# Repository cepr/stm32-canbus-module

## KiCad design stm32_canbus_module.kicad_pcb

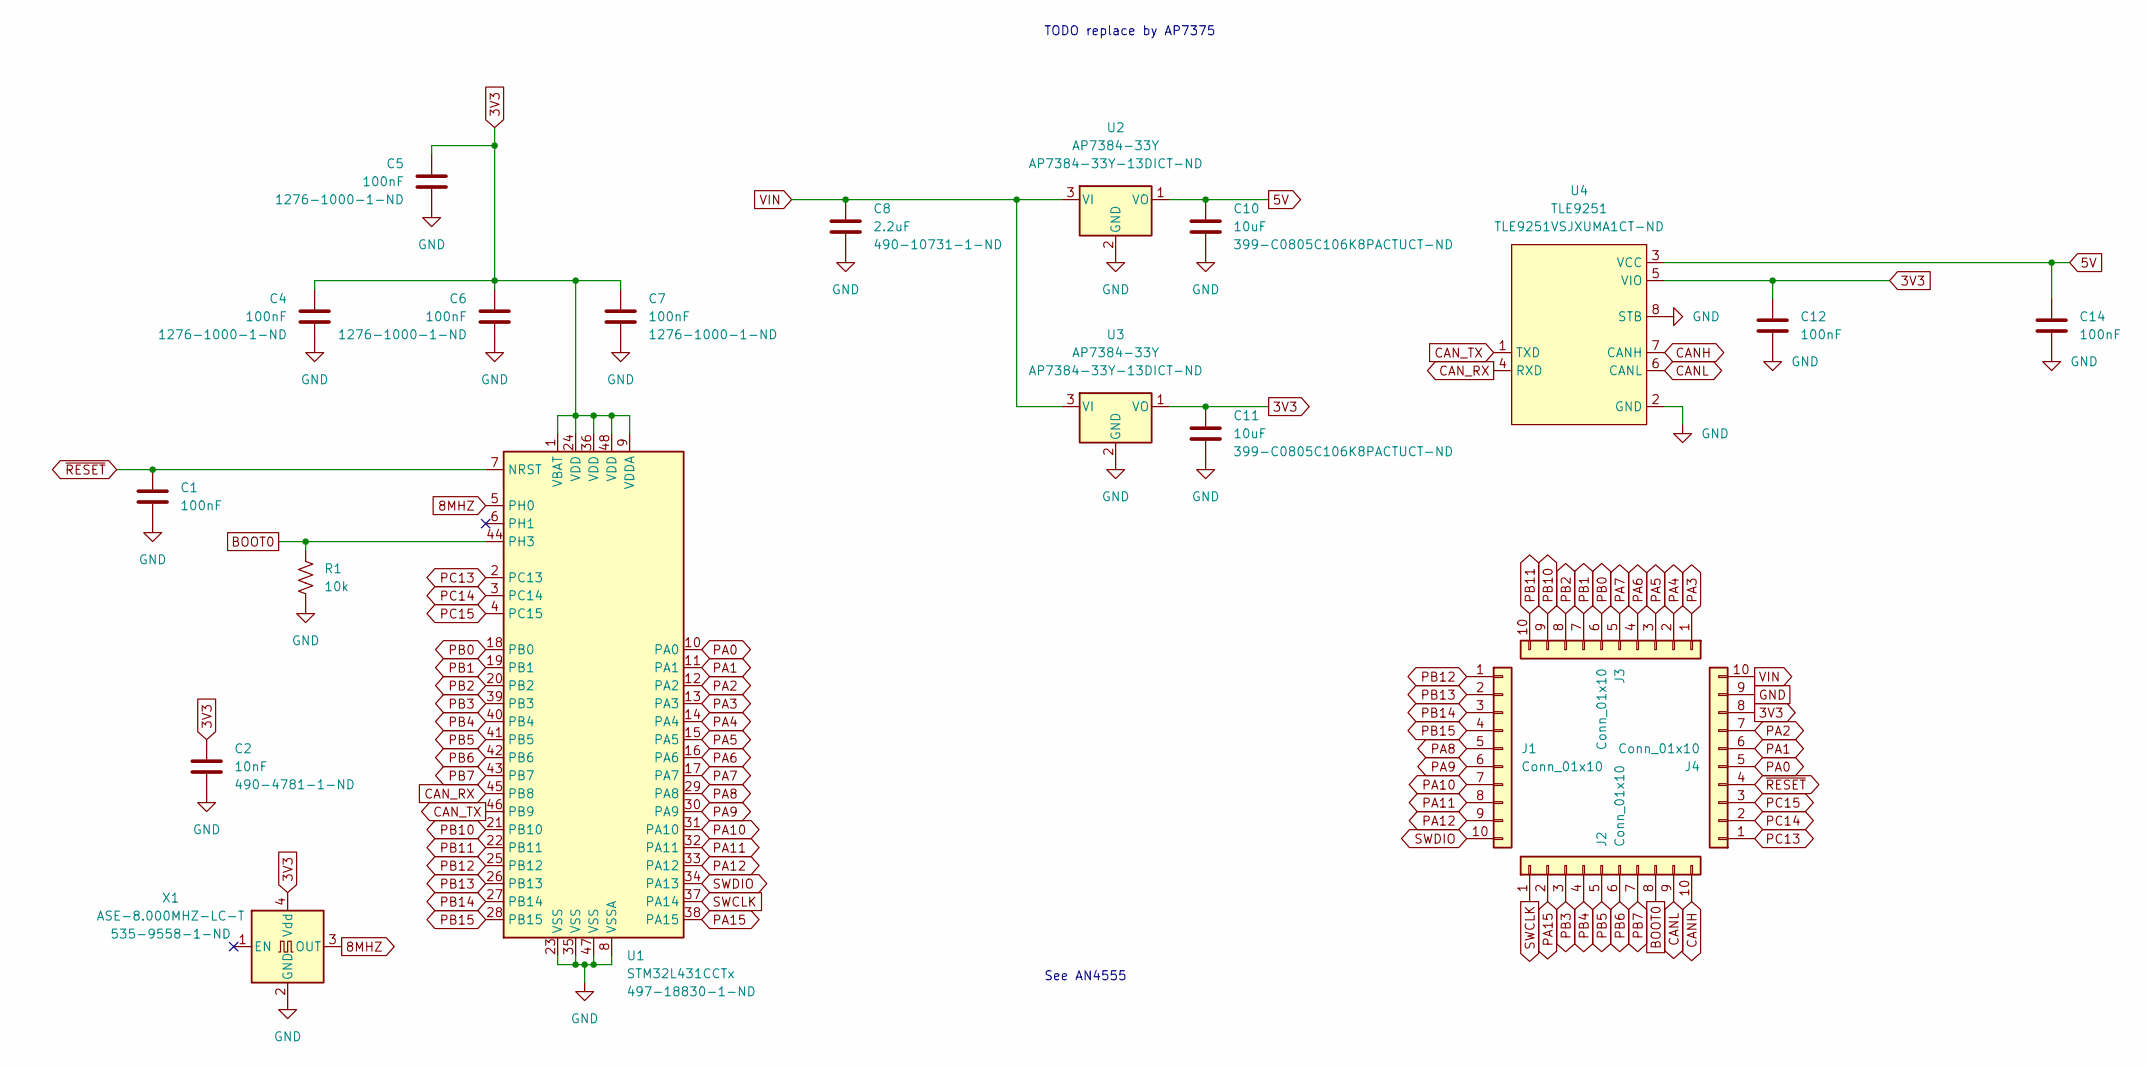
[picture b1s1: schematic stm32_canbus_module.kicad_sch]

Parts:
C1, C4, C5, C6, C7, C12, C14: 100nF; C_0603_1608Metric_Pad1.08x0.95mm_HandSolder; DigiKey 1276-1000-1-ND
C2: 10nF; C_0603_1608Metric_Pad1.08x0.95mm_HandSolder; DigiKey 490-4781-1-ND
C8: 2.2uF; C_0603_1608Metric_Pad1.08x0.95mm_HandSolder; DigiKey 490-10731-1-ND
C10, C11: 10uF; C_0805_2012Metric_Pad1.18x1.45mm_HandSolder; DigiKey 399-C0805C106K8PACTUCT-ND
J1, J2, J3, J4: Conn_01x10; PinHeader_1x10_P2.54mm_Vertical
R1: 10k; R_0603_1608Metric_Pad0.98x0.95mm_HandSolder; DigiKey RNCP0603FTD10K0CT-ND
U1: STM32L431CCTx; LQFP-48_7x7mm_P0.5mm; DigiKey 497-18830-1-ND
U2, U3: AP7384-33Y; SOT-89-3; DigiKey AP7384-33Y-13DICT-ND
U4: TLE9251; SOIC-8_3.9x4.9mm_P1.27mm; DigiKey TLE9251VSJXUMA1CT-ND
X1: ASE-8.000MHZ-LC-T; Oscillator_SMD_Abracon_ASE-4Pin_3.2x2.5mm_HandSoldering; DigiKey 535-9558-1-ND

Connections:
3V3: C2.1, C4.1, C5.1, C6.1, C7.1, C11.1, C12.1, J4.8, U1.1 (VBAT), U1.9 (VDDA), U1.24 (VDD), U1.36 (VDD), U1.48 (VDD), U3.1 (VO), U4.5 (VIO), X1.4 (Vdd)
5V: C10.1, C14.1, U2.1 (VO), U4.3 (VCC)
8MHZ: U1.5 (PH0), X1.3 (OUT)
BOOT0: J2.8, R1.2, U1.44 (PH3)
CANH: J2.10, U4.7 (CANH)
CANL: J2.9, U4.6 (CANL)
CAN_RX: U1.45 (PB8), U4.4 (RXD)
CAN_TX: U1.46 (PB9), U4.1 (TXD)
GND: C1.2, C2.2, C4.2, C5.2, C6.2, C7.2, C8.2, C10.2, C11.2, C12.2, C14.2, J4.9, R1.1, U1.8 (VSSA), U1.23 (VSS), U1.35 (VSS), U1.47 (VSS), U2.2 (GND), U3.2 (GND), U4.2 (GND), U4.8 (STB), X1.2 (GND)
PA0: J4.5, U1.10 (PA0)
PA1: J4.6, U1.11 (PA1)
PA2: J4.7, U1.12 (PA2)
PA3: J3.1, U1.13 (PA3)
PA4: J3.2, U1.14 (PA4)
PA5: J3.3, U1.15 (PA5)
PA6: J3.4, U1.16 (PA6)
PA7: J3.5, U1.17 (PA7)
PA8: J1.5, U1.29 (PA8)
PA9: J1.6, U1.30 (PA9)
PA10: J1.7, U1.31 (PA10)
PA11: J1.8, U1.32 (PA11)
PA12: J1.9, U1.33 (PA12)
PA15: J2.2, U1.38 (PA15)
PB0: J3.6, U1.18 (PB0)
PB1: J3.7, U1.19 (PB1)
PB2: J3.8, U1.20 (PB2)
PB3: J2.3, U1.39 (PB3)
PB4: J2.4, U1.40 (PB4)
PB5: J2.5, U1.41 (PB5)
PB6: J2.6, U1.42 (PB6)
PB7: J2.7, U1.43 (PB7)
PB10: J3.9, U1.21 (PB10)
PB11: J3.10, U1.22 (PB11)
PB12: J1.1, U1.25 (PB12)
PB13: J1.2, U1.26 (PB13)
PB14: J1.3, U1.27 (PB14)
PB15: J1.4, U1.28 (PB15)
PC13: J4.1, U1.2 (PC13)
PC14: J4.2, U1.3 (PC14)
PC15: J4.3, U1.4 (PC15)
SWCLK: J2.1, U1.37 (PA14)
SWDIO: J1.10, U1.34 (PA13)
VIN: C8.1, J4.10, U2.3 (VI), U3.3 (VI)
~RESET: C1.1, J4.4, U1.7 (NRST)

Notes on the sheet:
TODO replace by AP7375
See AN4555

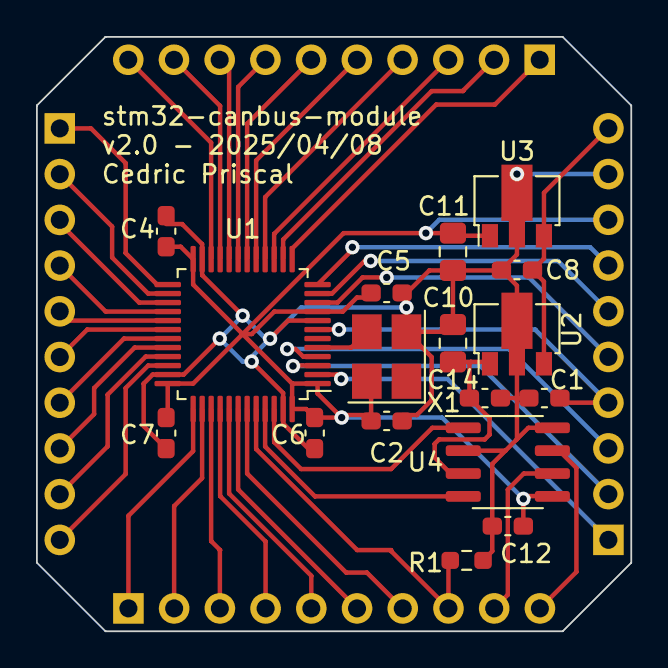
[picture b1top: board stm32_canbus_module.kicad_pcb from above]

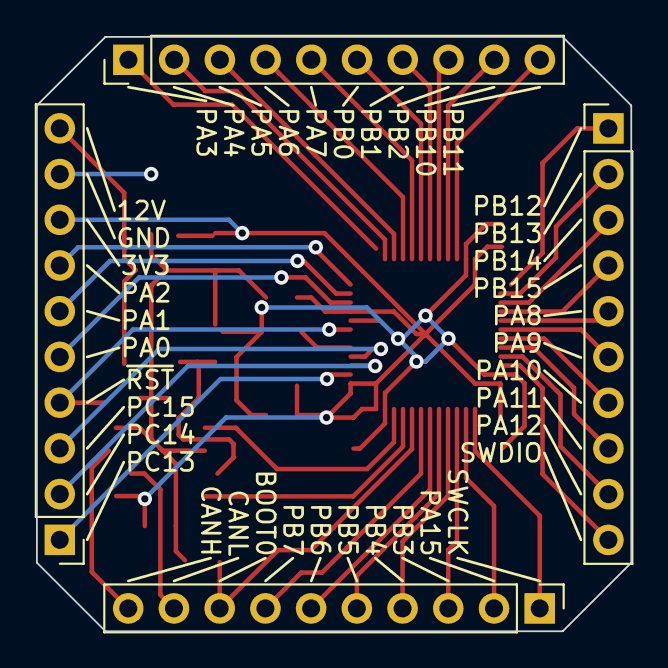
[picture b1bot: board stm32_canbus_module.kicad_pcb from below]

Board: 2 copper layers, 33.0 x 33.0 mm, 21 parts (4 on the bottom side), 44 nets.

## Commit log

2022-12-02 v1.0
2022-12-07 Updating BOM
2023-05-04 v1.1
2024-09-01 Migrating to Kicad 8, no change
2025-04-09 2.0
    - Adding 5V regulator, VIN now supports 12V
    - Migration to KiCad 9
